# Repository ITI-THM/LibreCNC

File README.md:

# LibreCNC

## Introduction

LibreCNC is a 100% open source circuit board repository for stepper driver powered CNC Machines of any kind. The circuit boards are designed to be modular with documented interfaces in between the boards.

Please check the [Success Stories](./Success%20Stories/) for a reference on how these boards can be used.

## Circuit Boards

The main modular circuit board is seperated in 3 parts:
- a [periphery board](#periphery-board) for stepper drivers, endstops and buttons
- a [logic board](#logic-board) for a (micro)controller
- a [power board](#power-board) for a stable power supply (tbd)

These parts have fixed interfaces that might be altered whenever a main version is changed (eg. from V1.x to V2.x).

### periphery board

current variations:
- [periphery_5_drivers](./periphery_5_drivers/README.md)

### logic board

current variations:
- [arduino-uno-connector](./arduino-uno-connector/README.md)

### power board

current variations:
None

Additionally these boards were created for specific tasks:
- [arduino pwm fan control board](./fan-control/README.md)

## Repository Structure

Each Circuit Board is designed with [KiCad](https://www.kicad.org/). 

The boards are stored within a directory with the corrsponding name.

Each directory consists of:
- a project file (.kicad_pro)
- a schematic file (.kicad_sch)
- a pcb file (.kicad_pcb)
- a gerber file directory storing gerber files of the finished versions
- a readme giving details about the board
- a picture of a 3D View of the board
- OPTIONAL: a list of parts

## Licencing 

All Circuit Boards are Licenced with the MIT Licence. Feel free to fork and experiment with the schematics and pcbs as you want.

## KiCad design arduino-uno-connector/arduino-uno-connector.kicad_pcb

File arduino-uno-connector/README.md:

# Arduino Connector

This board is connecting an arduino uno with the periphery board. 
It is designed to be used with [grbl](https://github.com/gnea/grbl) as running software.
Therefore the grbl pinouts are used.

## Driver Usage

- Driver A: X Axis
- Driver B: Y Axis (can be extended with Driver C for a Dual Axis)
- Driver D: Z Axis
- Driver E: Spindle

## Additional Infos

Please be aware of the following things:

- as long as the periphery board has no 5V or 3V3 Input, the 5V and 3V3 of the Arduino can be used.
- the board is designed in a way that the usb port is avaliable at the top of the board. If mounting within limited space be aware that the USB Port is outside the board size.

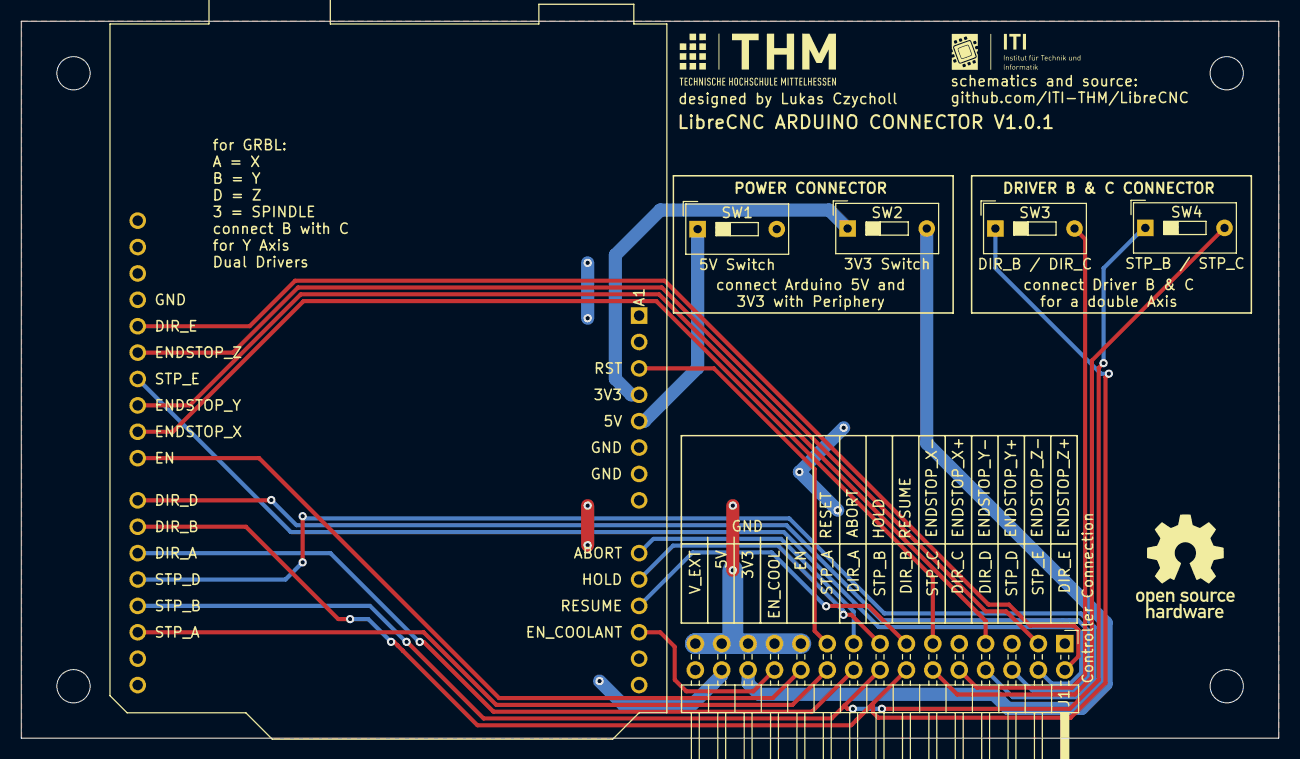
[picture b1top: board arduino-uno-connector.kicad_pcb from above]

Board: 2 copper layers, 121.0 x 69.0 mm, 10 parts (0 on the bottom side), 24 nets.

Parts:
A1: Arduino_UNO_R3
H1, H2, H3: MountingHole; MountingHole_3.2mm_M3
J1: Controller Connection; PinHeader_2x15_P2.54mm_Horizontal
SW1: 5V Switch; SW_DIP_SPSTx01_Slide_9.78x4.72mm_W7.62mm_P2.54mm
SW2: 3V3 Switch; SW_DIP_SPSTx01_Slide_9.78x4.72mm_W7.62mm_P2.54mm
SW3: DIR_B / DIR_C; SW_DIP_SPSTx01_Slide_9.78x4.72mm_W7.62mm_P2.54mm
SW4: STP_B / STP_C; SW_DIP_SPSTx01_Slide_9.78x4.72mm_W7.62mm_P2.54mm
locked: MountingHole; MountingHole_3.2mm_M3

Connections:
3V3: J1.26, SW2.2 (B)
3V3_Controller: A1.4 (3V3), SW2.1 (A)
5V: J1.28, SW1.2 (B)
5V_Controller: A1.5 (+5V), SW1.1 (A)
ABORT: A1.9 (A0), J1.17
DIR_A: A1.20 (D5), J1.18
DIR_B: A1.21 (D6), J1.14, SW3.1 (A)
DIR_C: J1.10, SW3.2 (B)
DIR_D: A1.22 (D7), J1.6
DIR_E: A1.28 (D13), J1.2
EN: A1.23 (D8), J1.22
ENDSTOP_X-: A1.24 (D9), J1.11
ENDSTOP_Y-: A1.25 (D10), J1.7
ENDSTOP_Z-: A1.27 (D12), J1.3
EN_COOLANT: A1.12 (A3), J1.24
GND: A1.6 (GND), A1.7 (GND), A1.29 (GND), J1.21, J1.23, J1.25, J1.27, J1.29
HOLD: A1.10 (A1), J1.15
RESUME: A1.11 (A2), J1.13
RST: A1.3 (~RESET), J1.19
STP_A: A1.17 (D2), J1.20
STP_B: A1.18 (D3), J1.16, SW4.1 (A)
STP_C: J1.12, SW4.2 (B)
STP_D: A1.19 (D4), J1.8
STP_E: A1.26 (D11), J1.4

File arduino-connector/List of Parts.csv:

Type,Quantity,Footprint,Designators
Switch,4,SW_DIP_SPSTx01_Slide_9.78x4.72mm_W7.62mm_P2.54mm,"SW1, SW2, SW3, SW4"
Pinheader 2x13,1,PinHeader_2x13_P2.54mm_Horizontal,J1
Pinsocket 1x 10,1,PinSocket_1x10_P2.54mm_Vertical,A1
Pinsocket 1x8,2,PinSocket_1x8_P2.54mm_Vertical,A1
Pinsocket 1x6,1,PinSocket_1x6_P2.54mm_Vertical,A1

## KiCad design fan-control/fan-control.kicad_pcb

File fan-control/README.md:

# arduino pwm fan control

A board designed to hold an arduino nano, a potentiometer and control up to 5 pwm fans

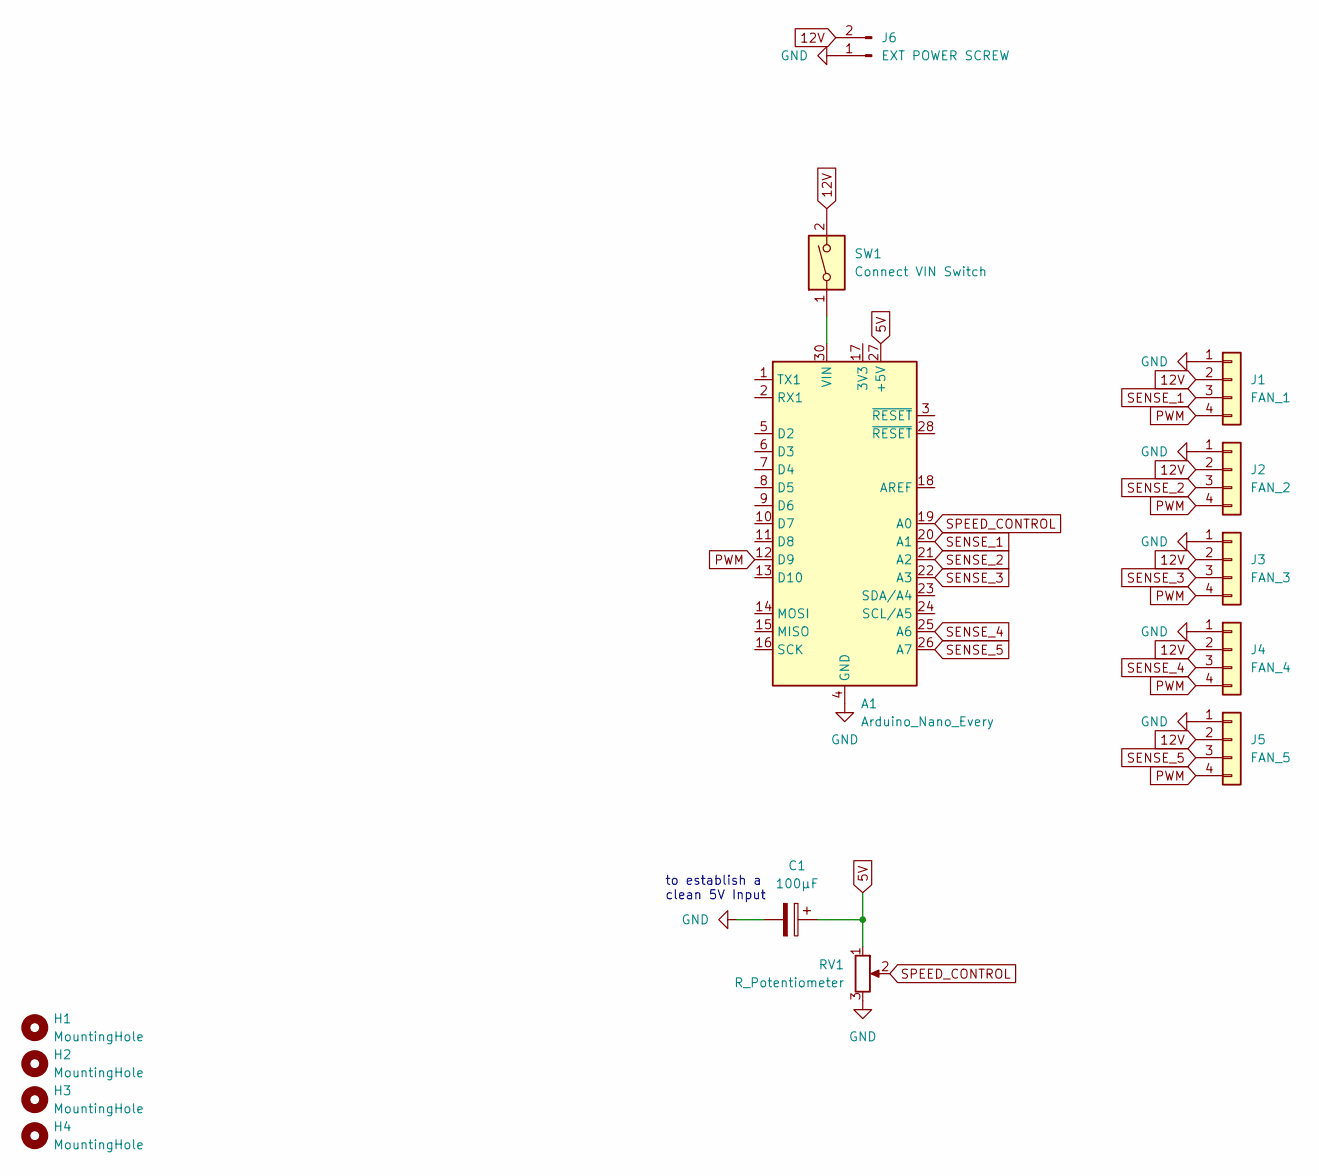
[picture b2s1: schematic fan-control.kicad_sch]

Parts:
A1: Arduino_Nano_Every; Arduino_Nano
C1: 100µF; CP_Radial_D6.3mm_P2.50mm
H1, H2, H3, H4: MountingHole; MountingHole_3.2mm_M3
J1: FAN_1; FanPinHeader_1x04_P2.54mm_Vertical
J2: FAN_2; FanPinHeader_1x04_P2.54mm_Vertical
J3: FAN_3; FanPinHeader_1x04_P2.54mm_Vertical
J4: FAN_4; FanPinHeader_1x04_P2.54mm_Vertical
J5: FAN_5; FanPinHeader_1x04_P2.54mm_Vertical
J6: EXT POWER SCREW; TerminalBlock_bornier-2_P5.08mm
RV1: R_Potentiometer; Potentiometer_Piher_PC-16_Single_Vertical
SW1: Connect VIN Switch; SW_DIP_SPSTx01_Slide_9.78x4.72mm_W7.62mm_P2.54mm

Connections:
5V: A1.27 (+5V), C1.1, RV1.1
12V: J1.2, J2.2, J3.2, J4.2, J5.2, J6.2, SW1.2
GND: A1.4 (GND), A1.29 (GND), C1.2, J1.1, J2.1, J3.1, J4.1, J5.1, J6.1, RV1.3
unnamed: A1.30 (VIN), SW1.1
PWM: A1.12 (D9), J1.4, J2.4, J3.4, J4.4, J5.4
SENSE_1: A1.20 (A1), J1.3
SENSE_2: A1.21 (A2), J2.3
SENSE_3: A1.22 (A3), J3.3
SENSE_4: A1.25 (A6), J4.3
SENSE_5: A1.26 (A7), J5.3
SPEED_CONTROL: A1.19 (A0), RV1.2

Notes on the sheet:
to establish a clean 5V Input

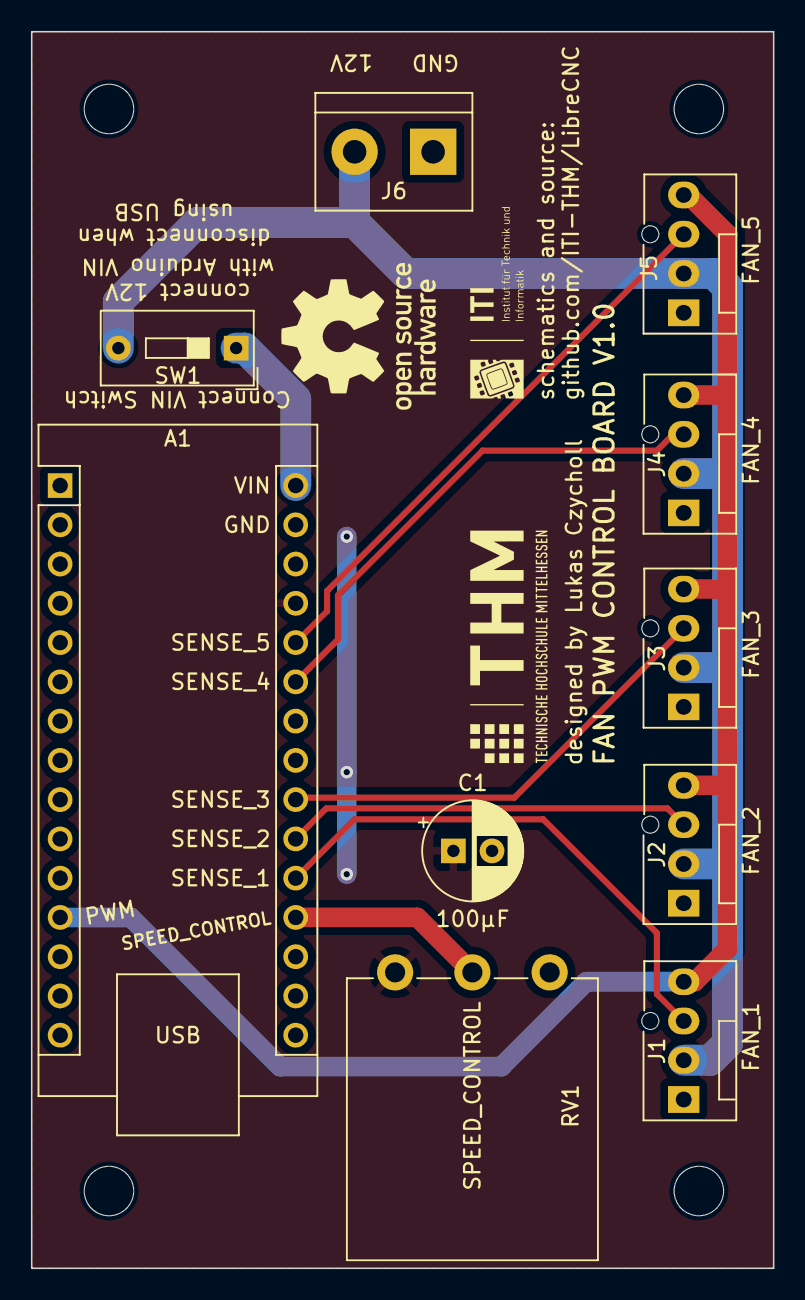
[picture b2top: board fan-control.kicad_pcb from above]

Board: 2 copper layers, 48.0 x 80.0 mm, 14 parts (0 on the bottom side), 11 nets.

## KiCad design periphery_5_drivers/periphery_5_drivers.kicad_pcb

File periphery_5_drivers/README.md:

# Periphery 5 Drivers

This board is holding periphery for the following:
- 5 stepper drivers
- 6 Endstops
- 5 Buttons
- signal forwarding
- power connections

## stepper drivers

The board is designed for A4988 drivers. 
Therefore any compatabile driver (like the TMC2209) can be used with this board.

## Endstops

the following (basic) endstops are supported:
- X+
- X-
- Y+
- Y-
- Z+
- Z-

Additionally there are switches to connect several endstops in order to be more compatible with different controllers.

- Y- to Z- and X- to Z- can be connected (as it is needed for specific machines)
- X-,Y- & Z- can be connected to the + part to use only one logic signal for both endstops

## Buttons

these buttons are supported:
- E-Stop
- Abort
- Hold
- Resume

The E-Stop signal can be inverted with a hardware switch.

To connect different buttons the signal can be connected to either 5V or GND

## Signal Forwarding

the following signals can be used by external periphery:
- EN
- DIR_E (eg. for an external Spindle)
- EN_COOL (eg. for an external Spindle)

## power connections

### Input: 
When using the periphery board without a power board, the power input screw connection can be used.
This input (as well as the power board input) is secured by a basic fuse.

### Output:
The board has the following power output connections:
- 2x 5V Screw Terminals
- 2x 12-36V Pins
- 2x 5V Pins
- 2x 3V3 Pins

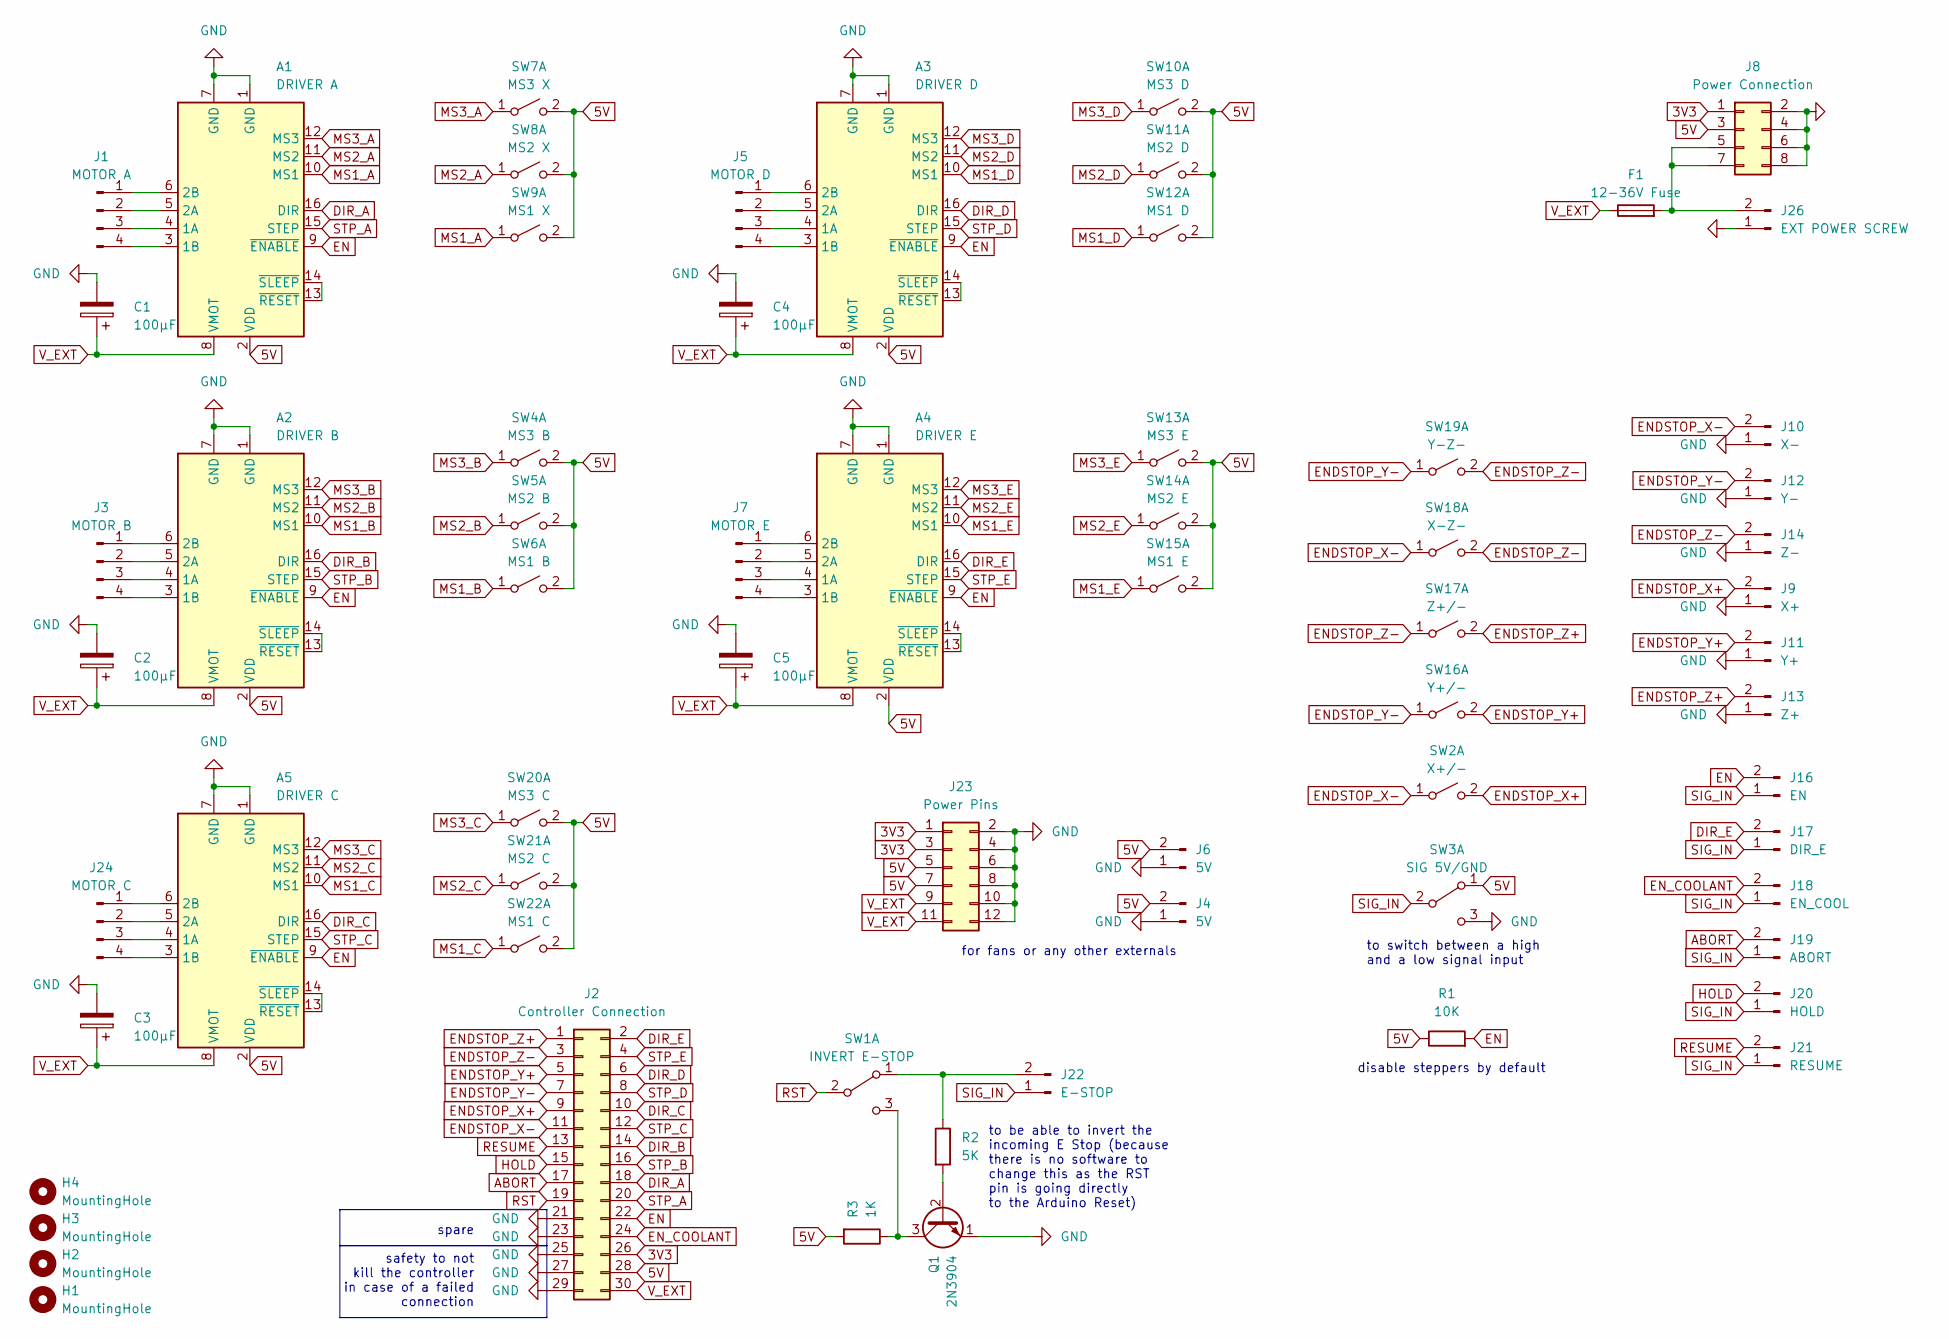
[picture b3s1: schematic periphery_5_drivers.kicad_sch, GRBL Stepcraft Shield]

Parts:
A1: DRIVER A; Pololu_Breakout-16_15.2x20.3mm
A2: DRIVER B; Pololu_Breakout-16_15.2x20.3mm
A3: DRIVER D; Pololu_Breakout-16_15.2x20.3mm
A4: DRIVER E; Pololu_Breakout-16_15.2x20.3mm
A5: DRIVER C; Pololu_Breakout-16_15.2x20.3mm
C1, C2, C3, C4, C5: 100µF; CP_Radial_D6.3mm_P2.50mm
F1: 12-36V Fuse; Fuseholder_Littelfuse_100_series_5x20mm
H1, H2, H3, H4: MountingHole; MountingHole_3.2mm_M3
J1: MOTOR A; TerminalBlock_bornier-4_P5.08mm
J2: Controller Connection; PinSocket_2x15_P2.54mm_Horizontal
J3: MOTOR B; TerminalBlock_bornier-4_P5.08mm
J4, J6: 5V; TerminalBlock_bornier-2_P5.08mm
J5: MOTOR D; TerminalBlock_bornier-4_P5.08mm
J7: MOTOR E; TerminalBlock_bornier-4_P5.08mm
J8: Power Connection; PinSocket_2x04_P2.54mm_Horizontal
J9: X+; TerminalBlock_bornier-2_P5.08mm
J10: X-; TerminalBlock_bornier-2_P5.08mm
J11: Y+; TerminalBlock_bornier-2_P5.08mm
J12: Y-; TerminalBlock_bornier-2_P5.08mm
J13: Z+; TerminalBlock_bornier-2_P5.08mm
J14: Z-; TerminalBlock_bornier-2_P5.08mm
J16: EN; TerminalBlock_bornier-2_P5.08mm
J17: DIR_E; TerminalBlock_bornier-2_P5.08mm
J18: EN_COOL; TerminalBlock_bornier-2_P5.08mm
J19: ABORT; TerminalBlock_bornier-2_P5.08mm
J20: HOLD; TerminalBlock_bornier-2_P5.08mm
J21: RESUME; TerminalBlock_bornier-2_P5.08mm
J22: E-STOP; TerminalBlock_bornier-2_P5.08mm
J23: Power Pins; PinSocket_2x06_P2.54mm_Vertical
J24: MOTOR C; TerminalBlock_bornier-4_P5.08mm
J26: EXT POWER SCREW; TerminalBlock_bornier-2_P5.08mm
Q1: 2N3904; TO-92_Inline_Wide
R1: 10K; R_Axial_DIN0207_L6.3mm_D2.5mm_P10.16mm_Horizontal
R2: 5K; R_Axial_DIN0207_L6.3mm_D2.5mm_P10.16mm_Horizontal
R3: 1K; R_Axial_DIN0207_L6.3mm_D2.5mm_P10.16mm_Horizontal
SW1: INVERT E-STOP; PinHeader_1x03_P2.54mm_Vertical
SW2: X+/-; SW_DIP_SPSTx01_Slide_9.78x4.72mm_W7.62mm_P2.54mm
SW3: SIG 5V/GND; PinHeader_1x03_P2.54mm_Vertical
SW4: MS3 B; SW_DIP_SPSTx01_Slide_9.78x4.72mm_W7.62mm_P2.54mm
SW5: MS2 B; SW_DIP_SPSTx01_Slide_9.78x4.72mm_W7.62mm_P2.54mm
SW6: MS1 B; SW_DIP_SPSTx01_Slide_9.78x4.72mm_W7.62mm_P2.54mm
SW7: MS3 X; SW_DIP_SPSTx01_Slide_9.78x4.72mm_W7.62mm_P2.54mm
SW8: MS2 X; SW_DIP_SPSTx01_Slide_9.78x4.72mm_W7.62mm_P2.54mm
SW9: MS1 X; SW_DIP_SPSTx01_Slide_9.78x4.72mm_W7.62mm_P2.54mm
SW10: MS3 D; SW_DIP_SPSTx01_Slide_9.78x4.72mm_W7.62mm_P2.54mm
SW11: MS2 D; SW_DIP_SPSTx01_Slide_9.78x4.72mm_W7.62mm_P2.54mm
SW12: MS1 D; SW_DIP_SPSTx01_Slide_9.78x4.72mm_W7.62mm_P2.54mm
SW13: MS3 E; SW_DIP_SPSTx01_Slide_9.78x4.72mm_W7.62mm_P2.54mm
SW14: MS2 E; SW_DIP_SPSTx01_Slide_9.78x4.72mm_W7.62mm_P2.54mm
SW15: MS1 E; SW_DIP_SPSTx01_Slide_9.78x4.72mm_W7.62mm_P2.54mm
SW16: Y+/-; SW_DIP_SPSTx01_Slide_9.78x4.72mm_W7.62mm_P2.54mm
SW17: Z+/-; SW_DIP_SPSTx01_Slide_9.78x4.72mm_W7.62mm_P2.54mm
SW18: X-Z-; SW_DIP_SPSTx01_Slide_9.78x4.72mm_W7.62mm_P2.54mm
SW19: Y-Z-; SW_DIP_SPSTx01_Slide_9.78x4.72mm_W7.62mm_P2.54mm
SW20: MS3 C; SW_DIP_SPSTx01_Slide_9.78x4.72mm_W7.62mm_P2.54mm
SW21: MS2 C; SW_DIP_SPSTx01_Slide_9.78x4.72mm_W7.62mm_P2.54mm
SW22: MS1 C; SW_DIP_SPSTx01_Slide_9.78x4.72mm_W7.62mm_P2.54mm

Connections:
3V3: J2.26, J8.1, J23.1, J23.3
5V: A1.2 (VDD), A2.2 (VDD), A3.2 (VDD), A4.2 (VDD), A5.2 (VDD), J2.28, J4.2, J6.2, J8.3, J23.5, J23.7, R1.1, R3.2, SW3.1 (A), SW4.2 (B), SW5.2 (B), SW6.2 (B), SW7.2 (B), SW8.2 (B), SW9.2 (B), SW10.2 (B), SW11.2 (B), SW12.2 (B), SW13.2 (B), SW14.2 (B), SW15.2 (B), SW20.2 (B), SW21.2 (B), SW22.2 (B)
ABORT: J2.17, J19.2
DIR_A: A1.16 (DIR), J2.18
DIR_B: A2.16 (DIR), J2.14
DIR_C: A5.16 (DIR), J2.10
DIR_D: A3.16 (DIR), J2.6
DIR_E: A4.16 (DIR), J2.2, J17.2
EN: A1.9 (~ENABLE), A2.9 (~ENABLE), A3.9 (~ENABLE), A4.9 (~ENABLE), A5.9 (~ENABLE), J2.22, J16.2, R1.2
ENDSTOP_X+: J2.9, J9.2, SW2.2 (B)
ENDSTOP_X-: J2.11, J10.2, SW2.1 (A), SW18.1 (A)
ENDSTOP_Y+: J2.5, J11.2, SW16.2 (B)
ENDSTOP_Y-: J2.7, J12.2, SW16.1 (A), SW19.1 (A)
ENDSTOP_Z+: J2.1, J13.2, SW17.2 (B)
ENDSTOP_Z-: J2.3, J14.2, SW17.1 (A), SW18.2 (B), SW19.2 (B)
EN_COOLANT: J2.24, J18.2
GND: A1.1 (GND), A1.7 (GND), A2.1 (GND), A2.7 (GND), A3.1 (GND), A3.7 (GND), A4.1 (GND), A4.7 (GND), A5.1 (GND), A5.7 (GND), C1.2, C2.2, C3.2, C4.2, C5.2, J2.21, J2.23, J2.25, J2.27, J2.29, J4.1, J6.1, J8.2, J8.4, J8.6, J8.8, J9.1, J10.1, J11.1, J12.1, J13.1, J14.1, J23.2, J23.4, J23.6, J23.8, J23.10, J23.12, J26.1, Q1.1 (E), SW3.3 (C)
HOLD: J2.15, J20.2
MS1_A: A1.10 (MS1), SW9.1 (A)
MS1_B: A2.10 (MS1), SW6.1 (A)
MS1_C: A5.10 (MS1), SW22.1 (A)
MS1_D: A3.10 (MS1), SW12.1 (A)
MS1_E: A4.10 (MS1), SW15.1 (A)
MS2_A: A1.11 (MS2), SW8.1 (A)
MS2_B: A2.11 (MS2), SW5.1 (A)
MS2_C: A5.11 (MS2), SW21.1 (A)
MS2_D: A3.11 (MS2), SW11.1 (A)
MS2_E: A4.11 (MS2), SW14.1 (A)
MS3_A: A1.12 (MS3), SW7.1 (A)
MS3_B: A2.12 (MS3), SW4.1 (A)
MS3_C: A5.12 (MS3), SW20.1 (A)
MS3_D: A3.12 (MS3), SW10.1 (A)
MS3_E: A4.12 (MS3), SW13.1 (A)
unnamed: A1.4 (1A), J1.3
unnamed: A1.3 (1B), J1.4
unnamed: A1.5 (2A), J1.2
unnamed: A1.6 (2B), J1.1
unnamed: A1.13 (~RESET), A1.14 (~SLEEP)
unnamed: A2.4 (1A), J3.3
unnamed: A2.3 (1B), J3.4
unnamed: A2.5 (2A), J3.2
unnamed: A2.6 (2B), J3.1
unnamed: A2.13 (~RESET), A2.14 (~SLEEP)
unnamed: A3.4 (1A), J5.3
unnamed: A3.3 (1B), J5.4
unnamed: A3.5 (2A), J5.2
unnamed: A3.6 (2B), J5.1
unnamed: A3.13 (~RESET), A3.14 (~SLEEP)
unnamed: A4.4 (1A), J7.3
unnamed: A4.3 (1B), J7.4
unnamed: A4.5 (2A), J7.2
unnamed: A4.6 (2B), J7.1
unnamed: A4.13 (~RESET), A4.14 (~SLEEP)
unnamed: A5.4 (1A), J24.3
unnamed: A5.3 (1B), J24.4
unnamed: A5.5 (2A), J24.2
unnamed: A5.6 (2B), J24.1
unnamed: A5.13 (~RESET), A5.14 (~SLEEP)
unnamed: J22.2, R2.1, SW1.1 (A)
unnamed: F1.2, J8.5, J8.7, J26.2
unnamed: Q1.2 (B), R2.2
unnamed: Q1.3 (C), R3.1, SW1.3 (C)
RESUME: J2.13, J21.2
RST: J2.19, SW1.2 (B)
SIG_IN: J16.1, J17.1, J18.1, J19.1, J20.1, J21.1, J22.1, SW3.2 (B)
STP_A: A1.15 (STEP), J2.20
STP_B: A2.15 (STEP), J2.16
STP_C: A5.15 (STEP), J2.12
STP_D: A3.15 (STEP), J2.8
STP_E: A4.15 (STEP), J2.4
V_EXT: A1.8 (VMOT), A2.8 (VMOT), A3.8 (VMOT), A4.8 (VMOT), A5.8 (VMOT), C1.1, C2.1, C3.1, C4.1, C5.1, F1.1, J2.30, J23.9, J23.11

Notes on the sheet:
safety to not kill the controller in case of a failed connection
for fans or any other externals
to be able to invert the incoming E Stop (because there is no software to change this as the RST pin is going directly to the Arduino Reset)
spare
to switch between a high and a low signal input
disable steppers by default

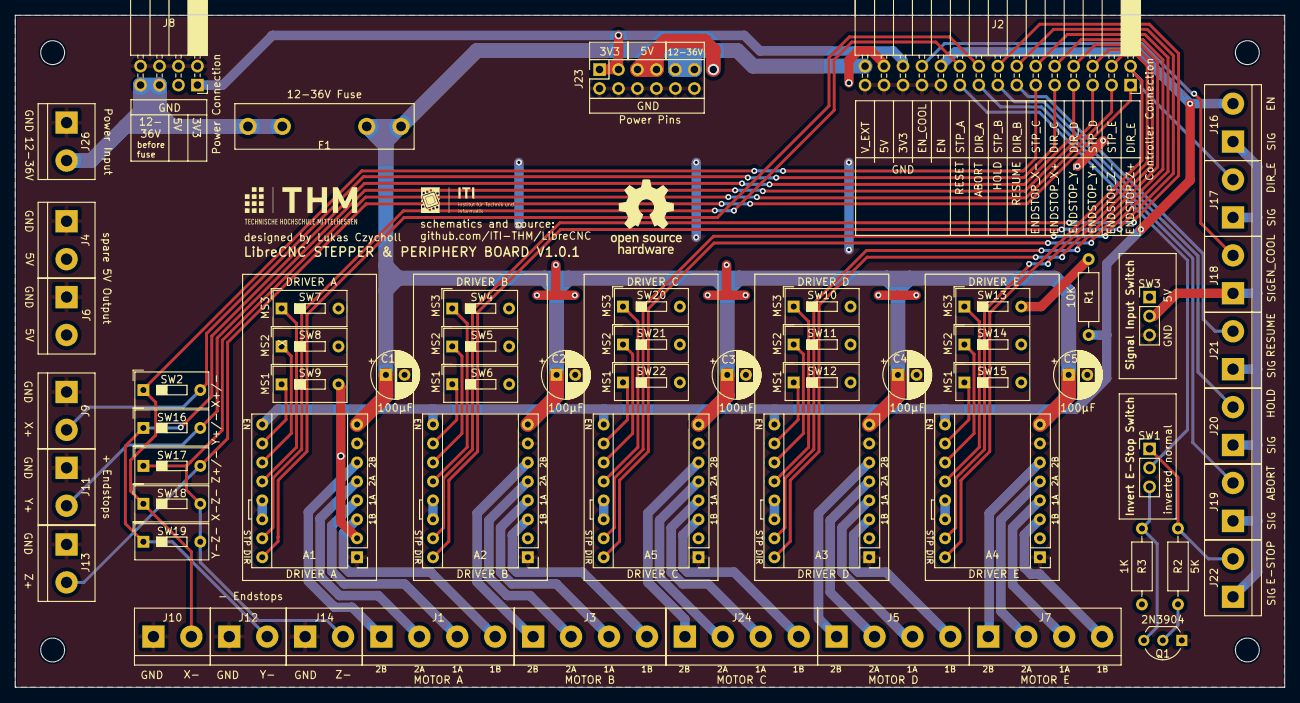
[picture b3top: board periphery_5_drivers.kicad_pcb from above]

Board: 2 copper layers, 170.0 x 90.0 mm, 65 parts (0 on the bottom side), 71 nets.

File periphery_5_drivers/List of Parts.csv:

Type,Quantity,Footprint,Designators
Screw Connector 4 Pol,4,"PhoenixContact_MC_1,5_4-G-5.08_1x04_P5.08mm_Horizontal","J1, J3, J5, J7, J24"
Screw Connector 2 Pol,14,"PhoenixContact_MC_1,5_4-G-5.08_1x04_P5.08mm_Horizontal","J4, J9, J10, J11, J12, J13, J14, J16, J17, J18 J19, J20, J21, J22"
Screw Connector 2 Pol Power,1,"PhoenixContact_MSTBA_2,5_2-G-5,08_1x02_P5.08mm_Horizontal",J26
Pinsocket 2x13,1,PinSocket_2x13_P2.54mm_Horizontal,J27
Pinsocket 2x2,1,PinSocket_2x2_P2.54mm_Horizontal,J6
Pinheader 2x6,1,PinHeader_2x06_P2.54mm_Vertical,J23
Pinsocket 1x8,10,,"A1, A2, A3, A4, A5"
Fuse Socket,1,Fuseholder_Littelfuse_100_series_5x20mm,F1
Switch 2 Pin,12,SW_DIP_SPSTx01_Slide_9.78x4.72mm_W7.62mm_P2.54mm,"SW4, SW5, SW6, SW7, SW8, SW9, SW10, SW11, SW12, SW13, SW14, SW15"
Switch 3 Pin,2,,"SW1, SW3"
Resistor 1K,1,R_Axial_DIN0204_L3.6mm_D1.6mm_P7.62mm_Horizontal,R3
Resistor 5K,1,R_Axial_DIN0204_L3.6mm_D1.6mm_P7.62mm_Horizontal,R2
Resistor 10K,1,R_Axial_DIN0204_L3.6mm_D1.6mm_P7.62mm_Horizontal,R1
Transistor 2N3904,1,TO-92_Inline,Q1
Capacitor 100µF,5,CP_Radial_D6.3mm_P2.50mm,"C1, C2, C3, C4, C5"

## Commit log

2023-12-21 Adding Circuit Board KiCad Files, Altered gitignore
2023-12-21 Added Gerber Files for each Circuit Board
2023-12-21 added readmes and updated naming of arduino connector
2024-01-02 added drill holes
2024-02-08 Updated Printing for Arduino and GRBL Reference
2024-02-12 Added a Success Story
2024-02-12 updated the success story with a cover section
2024-02-12 fixed the relative links for fan section Added a table of contents
2024-02-12 added a reference to the success stories
2024-02-12 cleaned up the success story folder
2024-02-12 updated z maximum travel option for grbl
